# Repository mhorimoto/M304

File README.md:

# M304
UECS Controller Shield for Arduino MEGA I/F

## 1. PARTS

### 1-1. NIC

DIPタイプのW5500チップを使用したNICを使用する．

Tzt smart electronics USR-ES
https://ja.aliexpress.com/item/4000226162371.html?spm=a2g0o.productlist.0.0.108b556fFrPpIG&algo_pvid=0f65874c-7d38-4736-bc98-e0055426879e&algo_exp_id=0f65874c-7d38-4736-bc98-e0055426879e-11&pdp_ext_f=%7B%22sku_id%22%3A%2210000000891679931%22%7D&pdp_npi=2%40dis%21JPY%21%21563.0%21%21%21311.0%21%21%402101e9d116535463700423560e6ebc%2110000000891679931%21sea

### 1-2. LCD

20x4 Parallel connection (秋月コード P-10844)

## 2. Pin Assign

### 2-1. LCD (J1)

| I/O PIN | NAME | LCD PIN |
|:-------:|------|:-------:|
|         | GND  |    1    |
|         | Vdd  |    2    |
|         | Vo   |    3    |
|   37    | RS   |    4    |
|   38    | R/W  |    5    |
|   39    | ENA  |    6    |
|   40    | DB0  |    7    |
|   41    | DB1  |    8    |
|   42    | DB2  |    9    |
|   43    | DB3  |   10    |
|   44    | DB4  |   11    |
|   45    | DB5  |   12    |
|   46    | DB6  |   13    |
|   47    | DB7  |   14    |
|         | BL+  |   15    |
|         | BL-  |   16    |

データピン８ピンすべて接続してある．

### 2-2. Relay OUT (J2)
リレー制御用のポートである．アクティブロー(負論理)である．

| J2 PIN | NAME |I/O PIN |
|:------:|------|:------:|
|    1   | RLY1 |   22   |
|    2   | RLY2 |   23   |
|    3   | RLY3 |   24   |
|    4   | RLY4 |   25   |
|    5   | RLY5 |   26   |
|    6   | RLY6 |   27   |
|    7   | RLY7 |   28   |
|    8   | RLY8 |   29   |
|    9   | Vdd  |   +5V  |

リレー制御の自動・手動状態検知のための端子(STAT)はI/O PIN=31である.

|状態|D31の状態|
|:--:|:-------:|
|自動|   H     |
|手動|   L     |

### 2-3. iM920 Interface (J3)
iM920用のインタフェースで3.3V駆動です.

| J3 PIN | NAME  | I/O PIN |
|:------:|-------|:-------:|
|    1   | RESET |    D6   |
|    2   | BUSY  |    D2   |
|    3   | GND   |   GND   |
|    4   | Vcc   |   3.3V  |
|    5   | TX    | D19(Rx) |
|    6   | RX    | D18(Tx) |
|    7   | STATUS|   D5    |

### 2-4. GNSS(GPS) Interface (J4)
秋月電子通商のGNSSキット用．

| J4 PIN | NAME  | I/O PIN  |
|:------:|-------|:--------:|
|    1   | 1PPS  |    D4    |
|    2   | RX    | D14(Tx3) |
|    3   | TX    | D15(Rx3) |
|    4   | GND   |   GND    |
|    5   | Vcc   |   +5V    |

### 2-5. Arrow Switch

アクティブローである．

| I/O PIN | 表示|回路図記号|
|:-------:|:---:|:----:|
|   32    | 決定 (SW_ENTER)| SW6 |
|   33    |  ↑ (SW_A) | SW2 |
|   34    |  ↓ (SW_B) | SW3 |
|   35    |  ← (SW_C) | SW4 |
|   36    |  → (SW_D) | SW5 |

### 2-6. 選択
ADCに接続している．ロータリーエンコーダの代わりにADCの出力を得て選択する．

| I/O PIN | 表示 | 回路図記号 |
|:----:|:-------------:|:---:|
|  A15 | 選択(SELECTOR) | RV2 |

### 2-7. RESET
リセットボタンはArduino MEGAのRESETピンへ直結していると同時にNICのRESETピンにも接続されている．アクティブローである．

### 2-8. SAFEMODE Switch
UECSの初期設定を行う際に必要となるスイッチ．UARDECS_Libraryの既定値である

| I/O PIN | 表示     | 回路図記号 |
|:----:|:----------------:|:---:|
|  D3  | 初期設定(SAFEMODE) | SW7 |

### 2-9. JA pins (Analog ports)
以下のピン配置で3.3V用8ポート，5V用7ポートがある．
ソフトウェアで入出力の両用に使える．

| XH PIN | 意味               |
|:------:|:------------------|
|    1   | GND               |
|    2   | CPUのAnalog port  |
|    3   | 電源 (3.3V or 5V)  |

コネクタとADCポートの関係

| PORT名 | 電圧 | I/O PIN |
|:-----:|:----:|:-------:|
|  JA0  | 3.3V |   A0    |
|  JA1  | 3.3V |   A1    |
|  JA2  | 3.3V |   A2    |
|  JA3  | 3.3V |   A3    |
|  JA4  | 3.3V |   A4    |
|  JA5  | 3.3V |   A5    |
|  JA6  | 3.3V |   A6    |
|  JA7  | 3.3V |   A7    |
|  JA8  |  5V  |   A8    |
|  JA9  |  5V  |   A9    |
|  JA10 |  5V  |   A10   |
|  JA11 |  5V  |   A11   |
|  JA12 |  5V  |   A12   |
|  JA13 |  5V  |   A13   |
|  JA14 |  5V  |   A14   |

### 2-10. JD pins (Digital ports)
以下のピン配置で7ポートある．ソフトウェアで入出力を切り替えられる．

| XH PIN | 意味                |
|:------:|:-------------------|
|    1   | GND                |
|    2   | CPUのDigital port  |

コネクタとDIOポートの関係

| PORT名 | I/O PIN |
|:-----:|:-------:|
|  JD7  |   D7    |
|  JD8  |   D8    |
|  JD9  |   D9    |
|  JD10 |   D10   |
|  JD11 |   D11   |
|  JD12 |   D12   |
|  JD13 |   D13   |

### 2-11. UART (JX2)
外部の装置とUART接続するためのポートが準備されている．
ポート名はJX2．電圧レベルは5V．接続先の送受関係は，2ピンに対象体のRxを3ピンにTxを接続する．

| XH PIN番号 | I/O PIN   |
|:---------:|:---------:|
|     1     | GND       |
|     2     | D16 (Tx2) |
|     3     | D17 (Rx2) |

### 2-12. TEST Pad
独自にテストを行う際の独立したDIO pinのパッド．

| Pad名 | I/O PIN |
|:-----:|:-------:|
| JD30  |   D30   |
| JD48  |   D48   |
| JD49  |   D49   |

### 2-13. I2C Devices

標準で搭載されているI2Cデバイスは以下の通り．

| Address | 名称            |
|:-------:|:----------------|
| 0x50    | EEPROM AT24C256 |
| 0x68    | RTC DS1307      |

* EEPROM
AT24C256 を使用している．32kBytesの容量がある．
* RTC (Address=0x68)
DS1307を使用してる．(DS1307RTC)

https://stackedit.io/app#

## 3.Software

### 3-1. AT24C256 EEPROM

データの保存を行う他に重要な役割がある．

UECS-IDとMACアドレスを以下のアドレスに記録する．MSB first，Big endianにて記録する．

|  Address      | Data        |
|:-------------:|:------------|
| 00H〜05H      | UECS-ID     |
| 06H〜0BH      | MAC Address |
| 0CH〜1FH      | Reserved    |
| 20H〜7FFFH    | Data        |

* UECS-ID: 10100C00000B
* MAC Address: 02:A2:73:0B:xx:xx

### 3-2. M304_Library

M304_Libraryは，M304を使用する際に初期化やポート名を決定してくれるヘッダファイルと若干の関数がまとめられたファイル．
現状では，Arduino-IDE(arduino-cli)が使用できるディレクトリにコピーして使う．
将来的には，このディレクトリから分離されて，Arduino-IDEなどのライブラリ管理から管理できるようにする．
同時にUARDECS_MEGAとの整合も図る．

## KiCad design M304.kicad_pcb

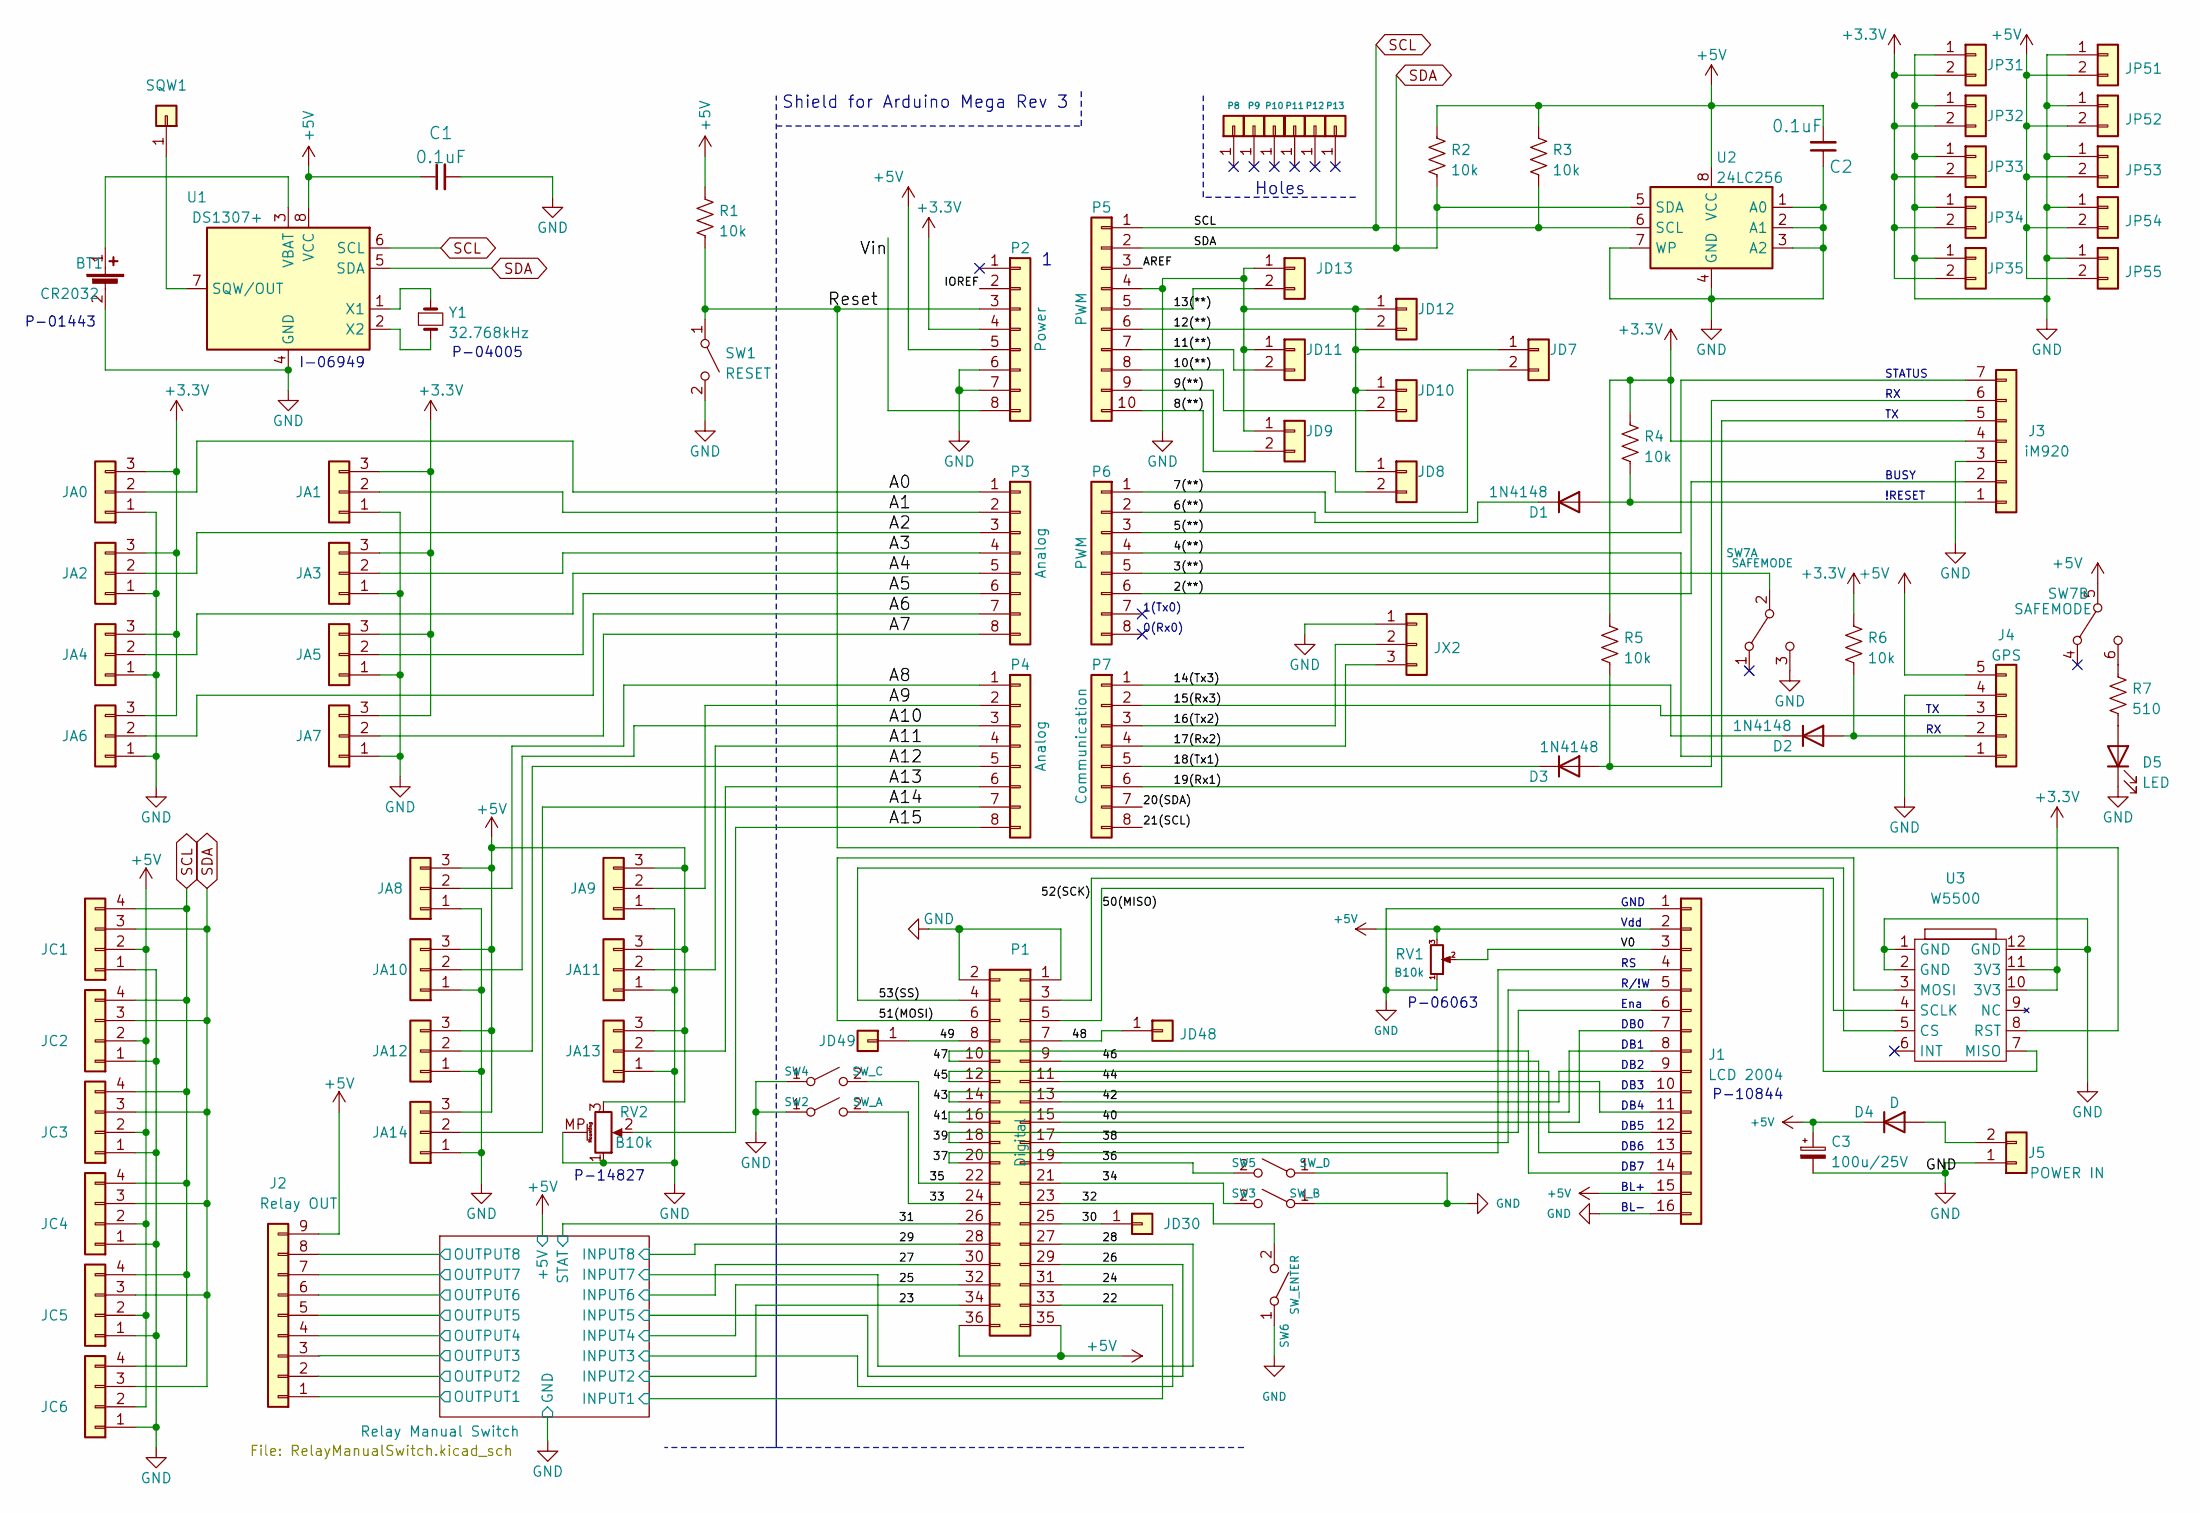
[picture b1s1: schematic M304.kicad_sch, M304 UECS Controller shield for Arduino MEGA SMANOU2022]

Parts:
BT1: CR2032; CH74-2032LF
C1, C2: 0.1uF; C_Disc_D3.0mm_W2.0mm_P2.50mm
C3: 100u/25V; CP_Radial_D5.0mm_P2.00mm
D1, D2, D3: 1N4148; D_DO-35_SOD27_P7.62mm_Horizontal
D4: D; D_DO-35_SOD27_P10.16mm_Horizontal
D5: LED; LED_D3.0mm
J1: LCD 2004; PinSocket_1x16_P2.54mm_Vertical
J2: Relay OUT; JST_XH_B9B-XH-A_1x09_P2.50mm_Vertical
J3: iM920; JST_XH_B7B-XH-A_1x07_P2.50mm_Vertical
J4: GPS; JST_XH_B5B-XH-A_1x05_P2.50mm_Vertical
J5: POWER IN; JST_VH_B2P-VH_1x02_P3.96mm_Vertical
JA0, JA1, JA2, JA3, JA4, JA5, JA6, JA7, JA8, JA9, JA10, JA11, JA12, JA13, JA14: Conn_01x03; JST_XH_B3B-XH-A_1x03_P2.50mm_Vertical
JC1, JC2, JC3, JC4, JC5, JC6: Conn_01x04; JST_XH_B4B-XH-A_1x04_P2.50mm_Vertical
JD7, JD8, JD9, JD10, JD11, JD12, JD13: Conn_01x02; JST_XH_B2B-XH-A_1x02_P2.50mm_Vertical
JD30, JD48, JD49: Conn_01x01; Pin_D0.9mm_L10.0mm_W2.4mm_FlatFork
JP31, JP32, JP33, JP34, JP35, JP51, JP52, JP53, JP54, JP55: Conn_01x02; JST_XH_B2B-XH-A_1x02_P2.50mm_Vertical
JX2: Conn_01x03; JST_XH_B3B-XH-A_1x03_P2.50mm_Vertical
P1: Digital; PinHeader_2x18_P2.54mm_Vertical
P2: Power; PinHeader_1x08_P2.54mm_Vertical
P3, P4: Analog; PinHeader_1x08_P2.54mm_Vertical
P5: PWM; PinHeader_1x10_P2.54mm_Vertical
P6: PWM; PinHeader_1x08_P2.54mm_Vertical
P7: Communication; PinHeader_1x08_P2.54mm_Vertical
P8, P9, P10, P11, P12, P13: CONN_01X01; Arduino_1pin
R1, R2, R3, R4, R5, R6: 10k; R_Axial_DIN0207_L6.3mm_D2.5mm_P7.62mm_Horizontal
R7: 510; R_Axial_DIN0207_L6.3mm_D2.5mm_P7.62mm_Horizontal
RV1: B10k; Potentiometer_Runtron_RM-065_Vertical
RV2: B10k; Potentiometer_Alps_RK09K_Single_Vertical
SQW1: Conn_01x01; Pin_D0.9mm_L10.0mm_W2.4mm_FlatFork
SW1: RESET; TVDT18-050
SW2: SW_A; TVDT18-050
SW3: SW_B; TVDT18-050
SW4: SW_C; TVDT18-050
SW5: SW_D; TVDT18-050
SW6: SW_ENTER; TVDT18-050
SW7: SAFEMODE; 2MD1T2B4M2QNS
U1: DS1307+; DIP-8_W7.62mm_LongPads
U2: 24LC256; DIP-8_W7.62mm_LongPads
U3: W5500
Y1: 32.768kHz; Crystal_C26-LF_D2.1mm_L6.5mm_Horizontal

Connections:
+3V3: J3.4, JA0.3, JA1.3, JA2.3, JA3.3, JA4.3, JA5.3, JA6.3, JA7.3, JP31.2, JP32.2, JP33.2, JP34.2, JP35.2, P2.4, R4.1, R5.1, R6.1, U3.10 (3V3), U3.11 (3V3)
+5V: C1.1, C2.2, C3.1, D4.1 (K), J1.2, J1.15, J2.9, J4.5, JA8.3, JA9.3, JA10.3, JA11.3, JA12.3, JA13.3, JA14.3, JC1.2, JC2.2, JC3.2, JC4.2, JC5.2, JC6.2, JP51.2, JP52.2, JP53.2, JP54.2, JP55.2, P1.35, P1.36, P2.5, R1.2, R2.1, R3.1, RV1.3, RV2.3, SW7.5 (B), U1.8 (VCC), U2.8 (VCC); also elsewhere on the board
/2(**): J3.2, P6.6
/3(**): P6.5, SW7.2 (B)
/4(**): J4.1, P6.4
/5(**): J3.7, P6.3
/6(**): D1.1 (K), P6.2
/7(**): JD7.2, P6.1
/8(**): JD8.2, P5.10
/9(**): JD9.2, P5.9
/10(**): JD10.2, P5.8
/11(**): JD11.2, P5.7
/12(**): JD12.2, P5.6
/13(**): JD13.2, P5.5
/14(Tx3): D2.1 (K), P7.1
/15(Rx3): J4.3, P7.2
/16(Tx2): JX2.2, P7.3
/17(Rx2): JX2.3, P7.4
/18(Tx1): D3.1 (K), P7.5
/19(Rx1): J3.5, P7.6
/20(SDA): P7.7
/21(SCL): P7.8
/22: P1.33; also elsewhere on the board
/23: P1.34; also elsewhere on the board
/24: P1.31; also elsewhere on the board
/25: P1.32; also elsewhere on the board
/26: P1.29; also elsewhere on the board
/27: P1.30; also elsewhere on the board
/28: P1.27; also elsewhere on the board
/29: P1.28; also elsewhere on the board
/30: JD30.1, P1.25
/31: P1.26; also elsewhere on the board
/32: P1.23, SW6.2 (B); also elsewhere on the board
/33: P1.24, SW2.2 (B)
/34: P1.21, SW3.2 (B)
/35: P1.22, SW4.2 (B)
/36: P1.19, SW5.2 (B)
/37: J1.4, P1.20
/38: J1.5, P1.17
/39: J1.6, P1.18
/40: J1.7, P1.15
/41: J1.8, P1.16
/42: J1.9, P1.13
/43: J1.10, P1.14
/44: J1.11, P1.11
/45: J1.12, P1.12
/46: J1.13, P1.9
/47: J1.14, P1.10
/48: JD48.1, P1.7
/49: JD49.1, P1.8
/50(MISO): P1.5, U3.7 (MISO)
/51(MOSI): P1.6, U3.3 (MOSI)
/52(SCK): P1.3, U3.4 (SCLK)
/53(SS): P1.4, U3.5 (CS)
/A0: JA0.2, P3.1
/A1: JA1.2, P3.2
/A2: JA2.2, P3.3
/A3: JA3.2, P3.4
/A4: JA4.2, P3.5
/A5: JA5.2, P3.6
/A6: JA6.2, P3.7
/A7: JA7.2, P3.8
/A8: JA8.2, P4.1
/A9: JA9.2, P4.2
/A10: JA10.2, P4.3
/A11: JA11.2, P4.4
/A12: JA12.2, P4.5
/A13: JA13.2, P4.6
/A14: JA14.2, P4.7
/A15: P4.8, RV2.2
/AREF: P5.3
/IOREF: P2.2
/Relay Manual Switch/OUTPUT1: J2.1; also elsewhere on the board
/Relay Manual Switch/OUTPUT2: J2.2; also elsewhere on the board
/Relay Manual Switch/OUTPUT3: J2.3; also elsewhere on the board
/Relay Manual Switch/OUTPUT4: J2.4; also elsewhere on the board
/Relay Manual Switch/OUTPUT5: J2.5; also elsewhere on the board
/Relay Manual Switch/OUTPUT6: J2.6; also elsewhere on the board
/Relay Manual Switch/OUTPUT7: J2.7; also elsewhere on the board
/Relay Manual Switch/OUTPUT8: J2.8; also elsewhere on the board
/Reset: P2.3, R1.1, SW1.1 (A), U3.8 (RST)
/V0: J1.3, RV1.2
/Vin: P2.8
GND: BT1.2 (-), C1.2, C2.1, C3.2, D5.1 (K), J1.1, J1.16, J3.3, J4.4, J5.1, JA0.1, JA1.1, JA2.1, JA3.1, JA4.1, JA5.1, JA6.1, JA7.1, JA8.1, JA9.1, JA10.1, JA11.1, JA12.1, JA13.1, JA14.1, JC1.1, JC2.1, JC3.1, JC4.1, JC5.1, JC6.1, JD7.1, JD8.1, JD9.1, JD10.1, JD11.1, JD12.1, JD13.1, JP31.1, JP32.1, JP33.1, JP34.1, JP35.1, JP51.1, JP52.1, JP53.1, JP54.1, JP55.1, JX2.1, P1.1, P1.2, P2.6, P2.7, P5.4, RV1.1, RV2.1, RV2.MP (MountPin), SW1.2 (B), SW2.1 (A), SW3.1 (A), SW4.1 (A), SW5.1 (A), SW6.1 (A), U1.4 (GND), U2.1 (A0), U2.2 (A1), U2.3 (A2), U2.4 (GND), U2.7 (WP), U3.1 (GND), U3.2 (GND), U3.12 (GND); also elsewhere on the board
unnamed: BT1.1 (+), U1.3 (VBAT)
unnamed: D1.2 (A), J3.1, R4.2
unnamed: D2.2 (A), J4.2, R6.2
unnamed: D3.2 (A), J3.6, R5.2
unnamed: D4.2 (A), J5.2
unnamed: D5.2 (A), R7.2
unnamed: R7.1, SW7.6 (C)
unnamed: SQW1.1, U1.7 (SQW/OUT)
unnamed: U1.1 (X1), Y1.1
unnamed: U1.2 (X2), Y1.2 (1)
SCL: JC1.4, JC2.4, JC3.4, JC4.4, JC5.4, JC6.4, P5.1, R3.2, U1.6 (SCL), U2.6 (SCL)
SDA: JC1.3, JC2.3, JC3.3, JC4.3, JC5.3, JC6.3, P5.2, R2.2, U1.5 (SDA), U2.5 (SDA)

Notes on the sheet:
DB5
P-10844
DB4
Ena
DB6
0(Rx0)
DB3
Vdd
BUSY
DB0
P-01443
R/!W
P-06063
DB1
GND
P-14827
I-06949
1(Tx0)
P-04005
Holes
BL+
STATUS
DB2
DB7
!RESET
BL-
Shield for Arduino Mega Rev 3

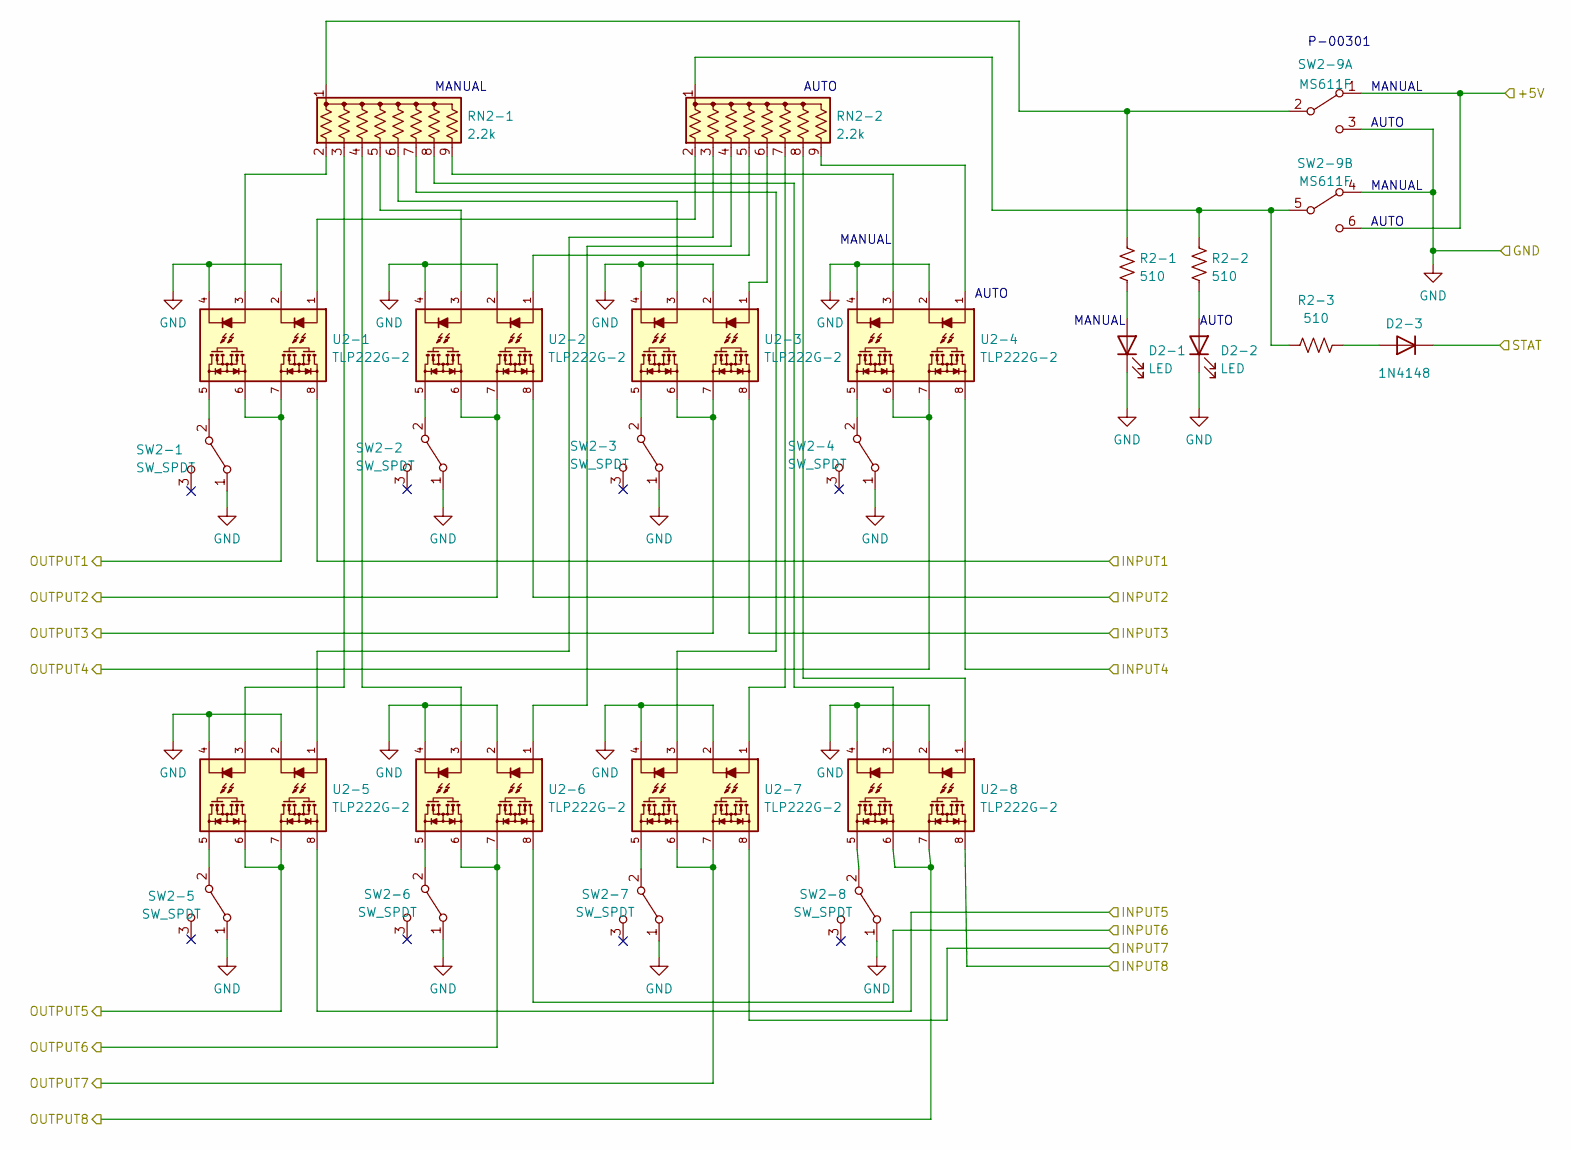
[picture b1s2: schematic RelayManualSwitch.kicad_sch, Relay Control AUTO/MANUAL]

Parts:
D2-1, D2-2: LED; LED_D3.0mm
D2-3: 1N4148; D_DO-35_SOD27_P7.62mm_Horizontal
R2-1, R2-2, R2-3: 510; R_Axial_DIN0207_L6.3mm_D2.5mm_P7.62mm_Horizontal
RN2-1, RN2-2: 2.2k; R_Array_SIP9
SW2-1, SW2-2, SW2-3, SW2-4, SW2-5, SW2-6, SW2-7, SW2-8: SW_SPDT; 2MS1T1B4M2QES
SW2-9: MS611F; 2MD1T2B4M2QNS
U2-1, U2-2, U2-3, U2-4, U2-5, U2-6, U2-7, U2-8: TLP222G-2; TLP222A-2

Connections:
+5V: SW2-9.1 (A), SW2-9.6 (C); also elsewhere on the board
/22: U2-1.8; also elsewhere on the board
/23: U2-2.8; also elsewhere on the board
/24: U2-3.8; also elsewhere on the board
/25: U2-4.8; also elsewhere on the board
/26: U2-5.8; also elsewhere on the board
/27: U2-6.8; also elsewhere on the board
/28: U2-7.8; also elsewhere on the board
/29: U2-8.8; also elsewhere on the board
/31: D2-3.1 (K); also elsewhere on the board
/Relay Manual Switch/OUTPUT1: U2-1.6, U2-1.7; also elsewhere on the board
/Relay Manual Switch/OUTPUT2: U2-2.6, U2-2.7; also elsewhere on the board
/Relay Manual Switch/OUTPUT3: U2-3.6, U2-3.7; also elsewhere on the board
/Relay Manual Switch/OUTPUT4: U2-4.6, U2-4.7; also elsewhere on the board
/Relay Manual Switch/OUTPUT5: U2-5.6, U2-5.7; also elsewhere on the board
/Relay Manual Switch/OUTPUT6: U2-6.6, U2-6.7; also elsewhere on the board
/Relay Manual Switch/OUTPUT7: U2-7.6, U2-7.7; also elsewhere on the board
/Relay Manual Switch/OUTPUT8: U2-8.6, U2-8.7; also elsewhere on the board
GND: D2-1.1 (K), D2-2.1 (K), SW2-1.1 (A), SW2-2.1 (A), SW2-3.1 (A), SW2-4.1 (A), SW2-5.1 (A), SW2-6.1 (A), SW2-7.1 (A), SW2-8.1 (A), SW2-9.3 (C), SW2-9.4 (A), U2-1.2, U2-1.4, U2-2.2, U2-2.4, U2-3.2, U2-3.4, U2-4.2, U2-4.4, U2-5.2, U2-5.4, U2-6.2, U2-6.4, U2-7.2, U2-7.4, U2-8.2, U2-8.4; also elsewhere on the board
unnamed: D2-1.2 (A), R2-1.2
unnamed: D2-2.2 (A), R2-2.2
unnamed: D2-3.2 (A), R2-3.2
unnamed: R2-1.1, RN2-1.1 (common), SW2-9.2 (B)
unnamed: R2-2.1, R2-3.1, RN2-2.1 (common), SW2-9.5 (B)
unnamed: RN2-1.2 (R1), U2-1.3
unnamed: RN2-1.3 (R2), U2-5.3
unnamed: RN2-1.4 (R3), U2-6.3
unnamed: RN2-1.5 (R4), U2-2.3
unnamed: RN2-1.6 (R5), U2-3.3
unnamed: RN2-1.7 (R6), U2-7.3
unnamed: RN2-1.8 (R7), U2-8.3
unnamed: RN2-1.9 (R8), U2-4.3
unnamed: RN2-2.2 (R1), U2-1.1
unnamed: RN2-2.3 (R2), U2-5.1
unnamed: RN2-2.4 (R3), U2-6.1
unnamed: RN2-2.5 (R4), U2-2.1
unnamed: RN2-2.6 (R5), U2-3.1
unnamed: RN2-2.7 (R6), U2-7.1
unnamed: RN2-2.8 (R7), U2-8.1
unnamed: RN2-2.9 (R8), U2-4.1
unnamed: SW2-1.2 (B), U2-1.5
unnamed: SW2-2.2 (B), U2-2.5
unnamed: SW2-3.2 (B), U2-3.5
unnamed: SW2-4.2 (B), U2-4.5
unnamed: SW2-5.2 (B), U2-5.5
unnamed: SW2-6.2 (B), U2-6.5
unnamed: SW2-7.2 (B), U2-7.5
unnamed: SW2-8.2 (B), U2-8.5

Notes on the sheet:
AUTO
MANUAL
P-00301

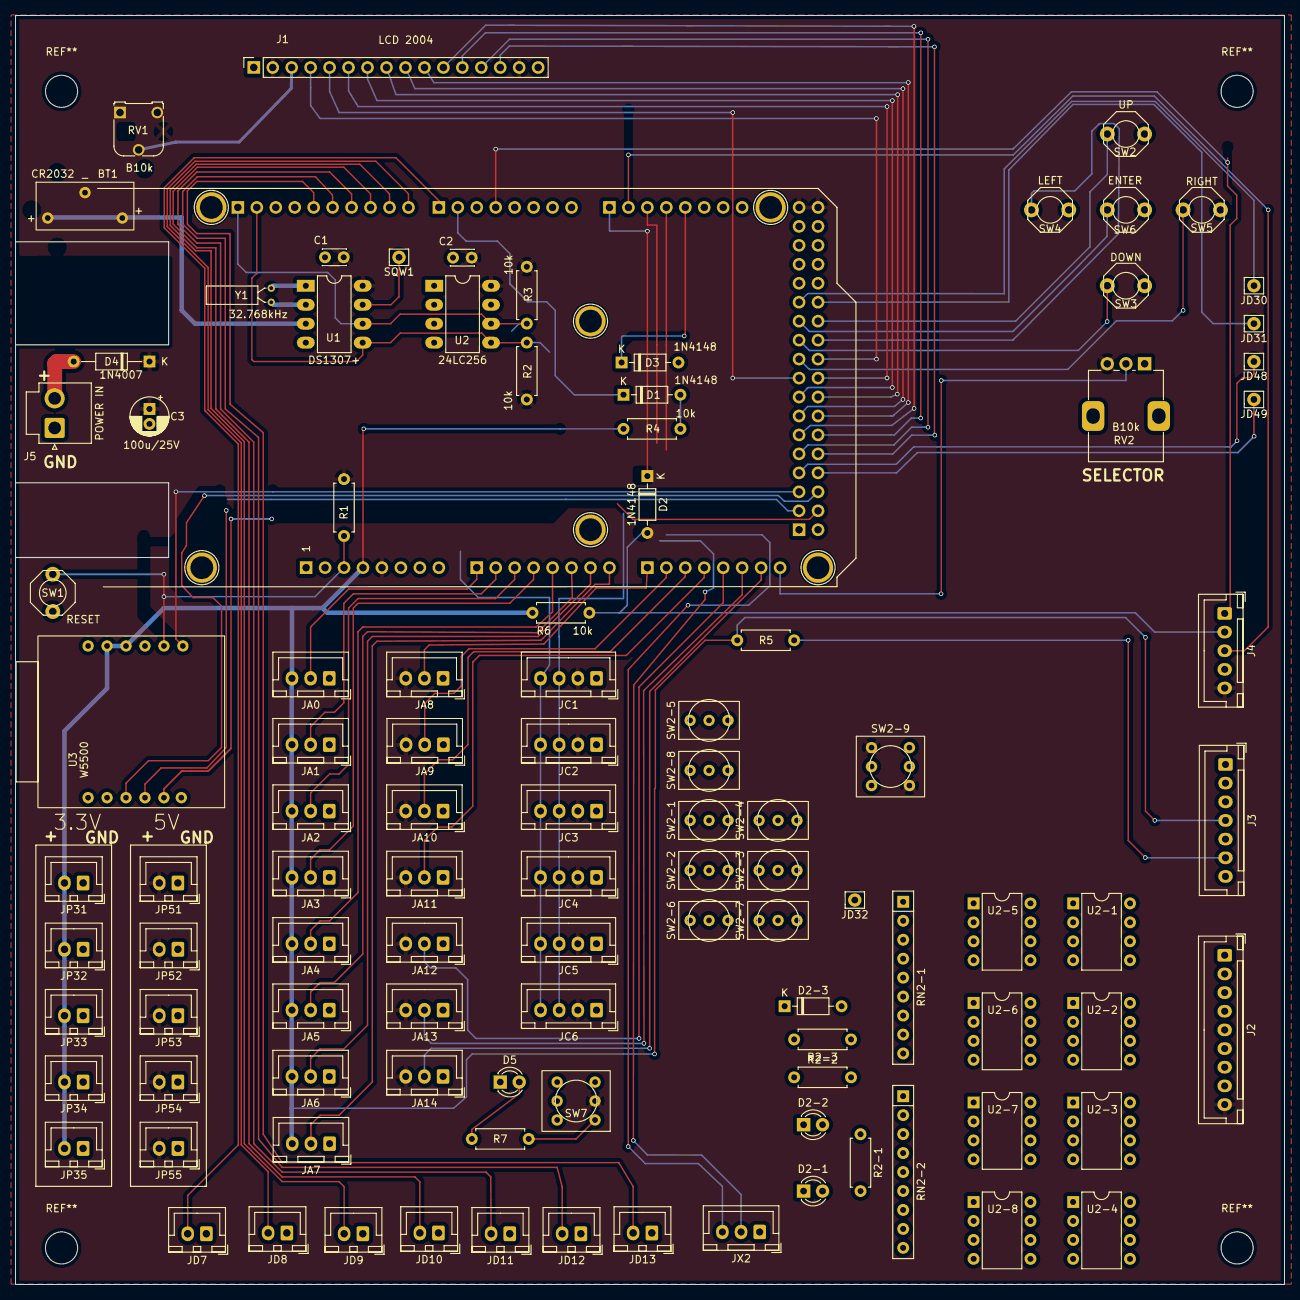
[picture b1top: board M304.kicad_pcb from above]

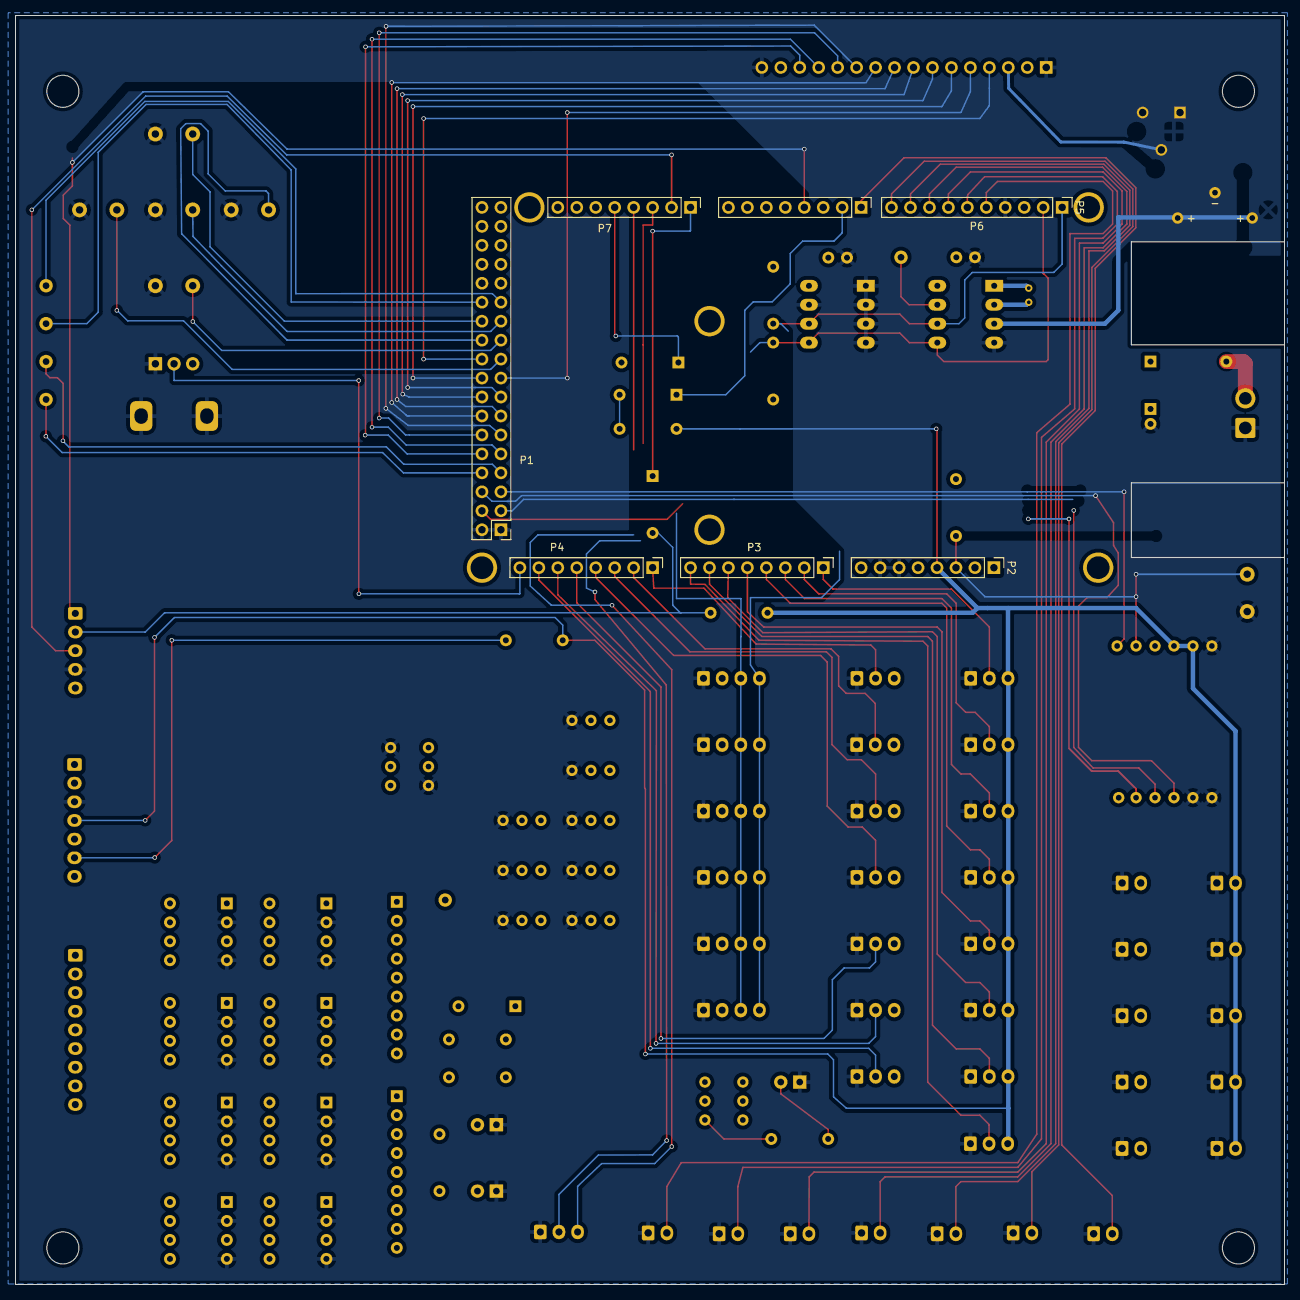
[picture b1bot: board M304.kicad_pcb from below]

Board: 2 copper layers, 170.0 x 170.0 mm, 117 parts (7 on the bottom side), 120 nets.

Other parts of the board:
JD31, JD32: Conn_01x01; Pin_D0.9mm_L10.0mm_W2.4mm_FlatFork

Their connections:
/31: JD31.1; also elsewhere on the board
/32: JD32.1; also elsewhere on the board

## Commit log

2022-05-27 KiCAD開始
2022-05-27 ignore file modified
2022-05-27 半分終了
2022-05-29 RTC追加
2022-06-02 Append RTC
2022-07-03 信号ラベルの見直し中
2022-07-05 回路だいたい出来た。
2022-07-07 PCB layout
2022-07-07 Arduino MEGA pin direction change
2022-07-07 Photo coupler append
2022-07-09 階層基板化中
2022-07-13 RelayManualSwitch回路充実
2022-07-17 Mode STAT monitoring
2022-07-19 PCB Design start
2022-07-19 PCB Design cont.
2022-07-20 コミット忘れ？
2022-07-20 PCB少し変更
2022-07-22 UECS/MANUAL 切り替え表示LED
2022-07-22 PCB随分と考え中
2022-07-24 PCB設計中
2022-07-24 print属性変更
2022-07-25 W5500周囲の変更
2022-07-26 部品リストにAKICODEを追加した
2022-07-29 parts list 更新
2022-07-31 スイッチ周りの配線を残すのみ
2022-08-01 一応完成、粗熱を取る
2022-08-01 シルク印刷を日本語化・スマ農塾向けだけ
2022-08-02 LCDの3Dイメージを追加とCAMOUTを出力しPCB屋さんで試す。
2022-08-02 3.3V三端子レギュレータを追加し、RTC回路を階層図面化
2022-08-03 部品リスト更新
2022-08-04 3D data re-assigned
2022-08-08 ガーバー出力・発注
2022-08-17 docs: Port and Pin assign
2022-08-18 docs: Append Port and Pin assign
2022-08-18 docs: feat: pin assign append and create tp
2022-08-18 docs: pin assign append
2022-08-20 Add test program
2022-08-22 TP002 create
2022-08-24 tp002,tp003を追加
2022-08-25 prog: add tp004
2022-08-28 prog: M304_Libraryの追加とTP004までの変更
2022-08-31 docs,prog: tp004 modified
2022-09-06 prog: tp005 and M304_Library
2022-09-07 docs: I2Cアドレス追記
2022-10-11 feat: tp006 append
2022-10-12 feat: tp007追加
2022-11-21 docs: add schematic PDF
2022-11-23 feat: tp006,tp007 append
2022-11-25 feat: RTCとの組み合わせ
2022-11-27 feat: GPS and SARA-R4 Append
2022-11-30 feat: GPSモジュール初期化プログラム
2022-12-20 prog: add tp008
2022-12-30 feat: tp008 cross switch subroutine
2022-12-31 feat: add getNumberValue()
2023-03-16 docs:MAC Address sample
2023-03-30 prog: Library
2023-04-01 docs: READMEを増やす
2023-04-19 prog: LCDなどのmethod追加
2023-05-03 prog: headerファイルにバージョンを反映させるようにしてコンパイルエラーを避けるようにした
2023-05-04 prog: IntWrite()の改良とヘッダにバージョンを記す
2023-05-06 docs,prog:
2023-05-08 prog: cmenuの追加など
2023-05-10 IPAdressWrite
2023-05-11 prog: IPWrite
2023-05-15 prog: モード値の変更
2023-05-15 prog: 1.07
2023-05-17 prog: 0.14
2023-05-22 prog: 0.20C
2023-05-22 prog: tp003 RLY1 check
2023-05-22 prog:
2023-05-31 rels: M304-Kansui v1.00
2023-12-23 ver: KiCAD version update
2023-12-23 ver: KiCAD Version match
2024-04-25 KiCAD Version 8.0
2024-06-22 3D data 編集 Tactile-Swiitch-FSM8JRT-WHITE.step SPDT-vertical-toggle-switch.step DPDT-vertical-toggle-switch-B-22AP.step
2025-01-28 Lab Support九州 ヴァージョン
